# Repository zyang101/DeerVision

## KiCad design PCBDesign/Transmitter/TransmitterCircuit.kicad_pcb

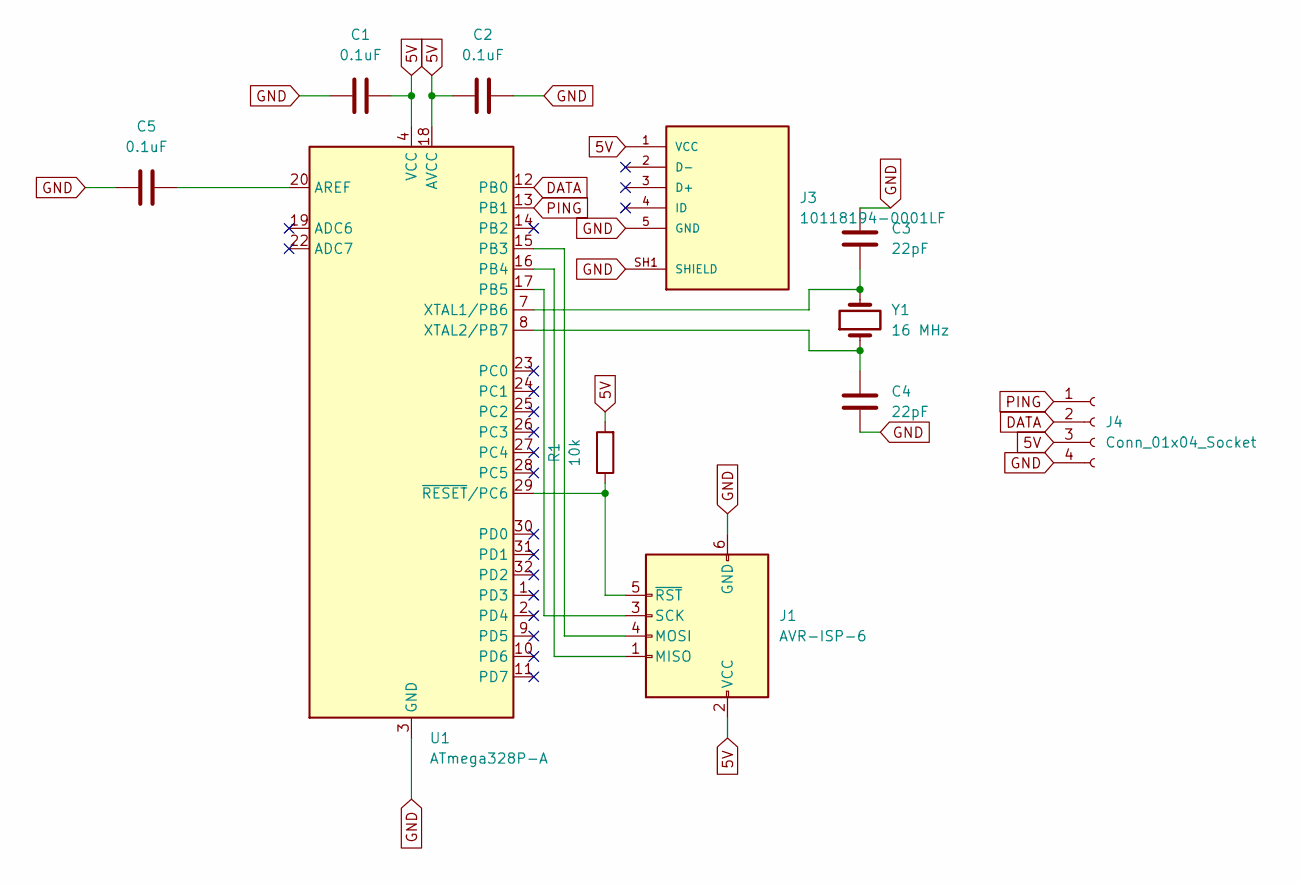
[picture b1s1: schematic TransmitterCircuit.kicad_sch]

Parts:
C1, C2, C5: 0.1uF; C_0805_2012Metric
C3, C4: 22pF; C_0805_2012Metric
J1: AVR-ISP-6; PinHeader_2x03_P2.54mm_Vertical
J3: 10118194-0001LF; AMPHENOL_10118194-0001LF; PARTREV D
J4: Conn_01x04_Socket; PinSocket_1x04_P2.54mm_Vertical
R1: 10k; R_0805_2012Metric
U1: ATmega328P-A; TQFP-32_7x7mm_P0.8mm
Y1: 16 MHz; Crystal_HC49-U_Vertical

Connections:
5V: C1.2, C2.1, J1.2 (VCC), J3.1 (VCC), J4.3, R1.2, U1.4 (VCC), U1.6 (VCC), U1.18 (AVCC)
DATA: J4.2, U1.12 (PB0)
GND: C1.1, C2.2, C3.2, C4.1, C5.1, J1.6 (GND), J3.5 (GND), J3.SH1 (SHIELD), J3.SH2 (SHIELD), J3.SH3 (SHIELD), J3.SH4 (SHIELD), J3.SH5 (SHIELD), J3.SH6 (SHIELD), J4.4, U1.3 (GND), U1.5 (GND), U1.21 (GND)
unnamed: J1.1 (MISO), U1.16 (PB4)
unnamed: J1.4 (MOSI), U1.15 (PB3)
unnamed: J1.3 (SCK), U1.17 (PB5)
unnamed: J1.5 (~RST), R1.1, U1.29 (~RESET/PC6)
unnamed: C5.2, U1.20 (AREF)
unnamed: C3.1, U1.7 (XTAL1/PB6), Y1.2
unnamed: C4.2, U1.8 (XTAL2/PB7), Y1.1
PING: J4.1, U1.13 (PB1)

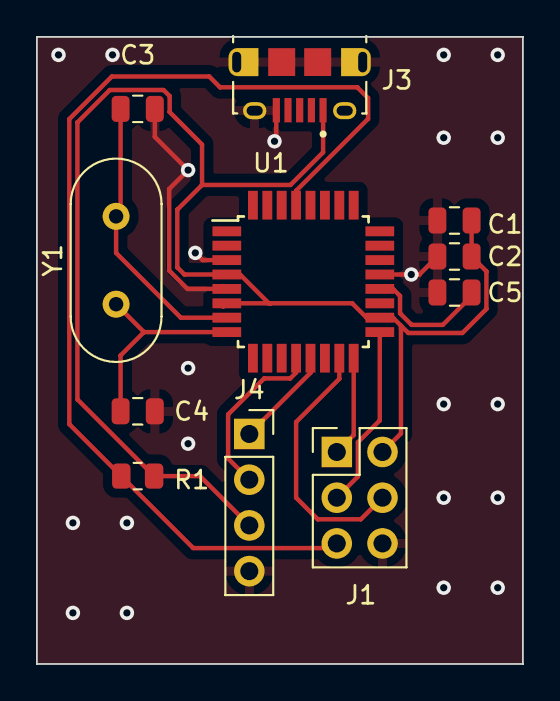
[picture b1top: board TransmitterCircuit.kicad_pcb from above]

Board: 2 copper layers, 27.0 x 34.8 mm, 11 parts (0 on the bottom side), 11 nets.

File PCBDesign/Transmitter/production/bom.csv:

Designator,Footprint,Quantity,Value,LCSC Part #
"C1, C2, C5",0805,3,0.1uF,
"C3, C4",0805,2,22pF,
J1,PinHeader_2x03_P2.54mm_Vertical,1,AVR-ISP-6,
J2,PinSocket_1x03_P2.54mm_Vertical,1,RF_TX_HEADER,
J3,AMPHENOL_10118194-0001LF,1,10118194-0001LF,
R1,0805,1,10k,
U1,TQFP-32_7x7mm_P0.8mm,1,ATmega328P-A,
Y1,Crystal_HC49-U_Vertical,1,16 MHz,
